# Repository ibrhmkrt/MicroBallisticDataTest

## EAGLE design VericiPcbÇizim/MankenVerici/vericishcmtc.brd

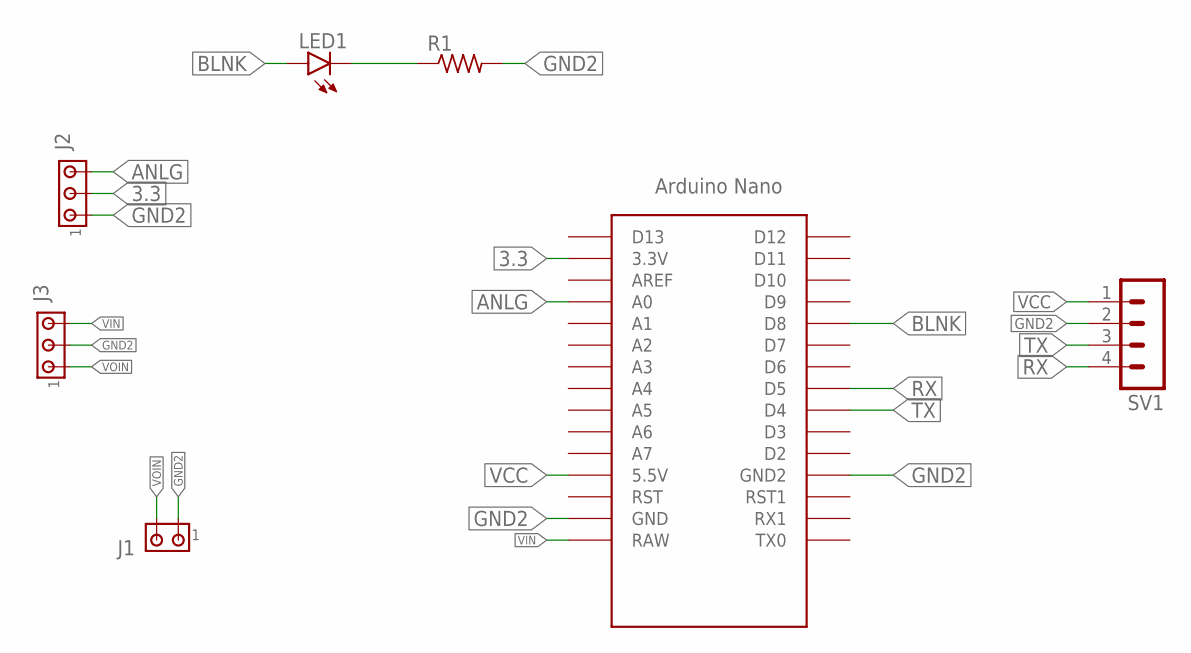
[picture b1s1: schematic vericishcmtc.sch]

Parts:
J1: MTA02-100; 10X02MTA
J2, J3: MTA03-100; 10X03MTA
LED1: LED5MM
R1: R-US_0204/5; 0204/5
SV1: MA04-1
U$1: NANO

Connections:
3.3: J2.2, U$1.3.3V
ANLG: J2.3, U$1.A0
BLNK: LED1.A, U$1.D8
GND2: J1.1, J2.1, J3.2, R1.2, SV1.2, U$1.GND, U$1.GND1 (GND2)
unnamed: LED1.K (C), R1.1
RX: SV1.4, U$1.D5
TX: SV1.3, U$1.D4
VCC: SV1.1, U$1.5V (5.5V)
VIN: J3.3, U$1.RAW
VOIN: J1.2, J3.1

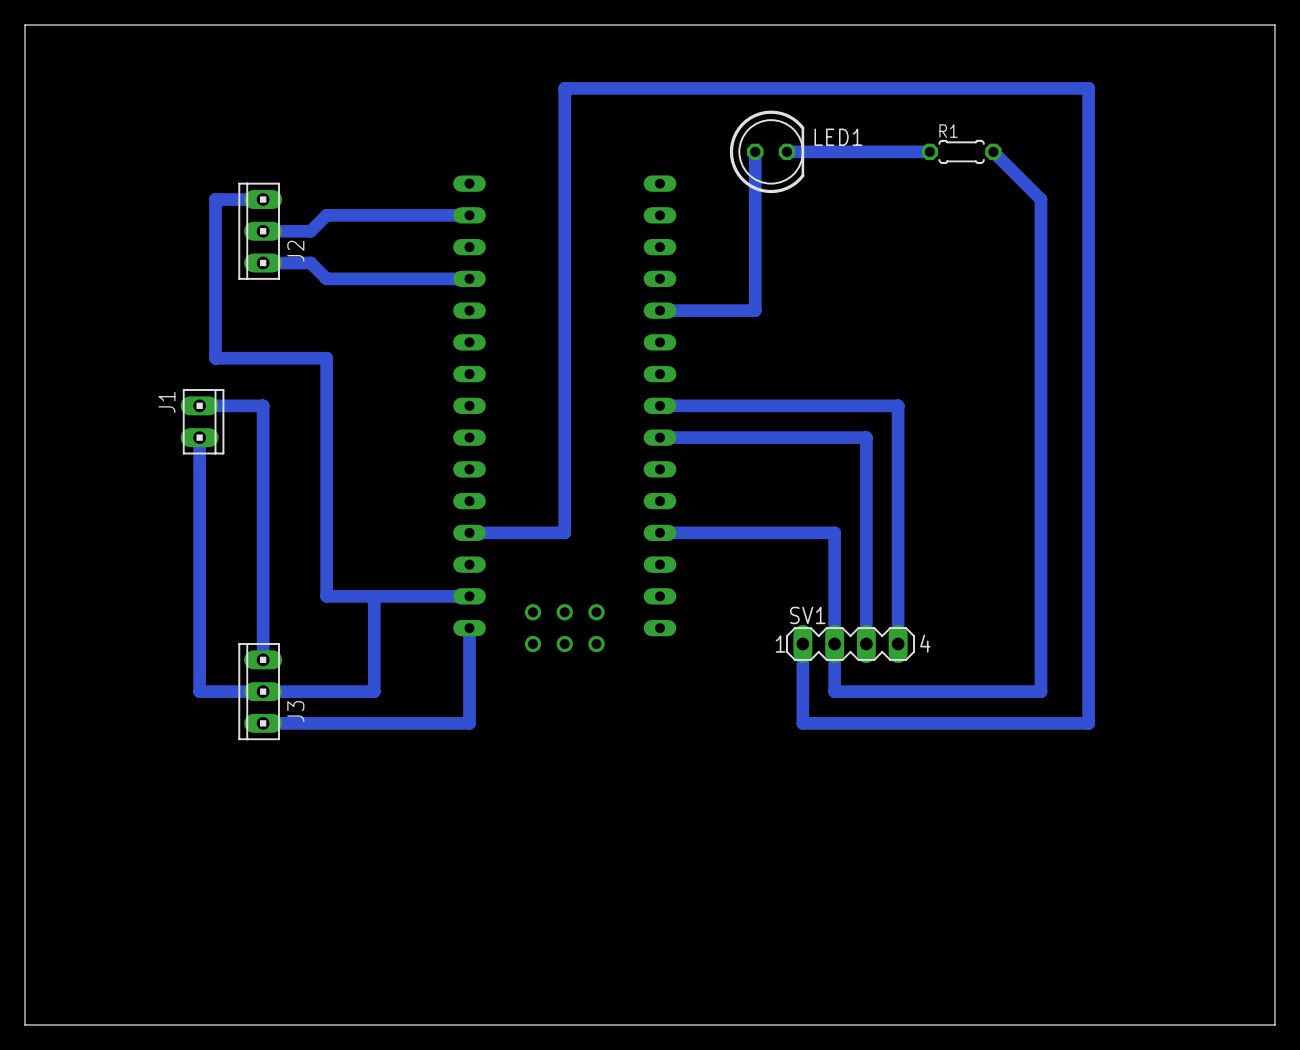
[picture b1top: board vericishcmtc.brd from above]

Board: 2 copper layers, 100.0 x 80.0 mm, 7 parts (0 on the bottom side), 10 nets.

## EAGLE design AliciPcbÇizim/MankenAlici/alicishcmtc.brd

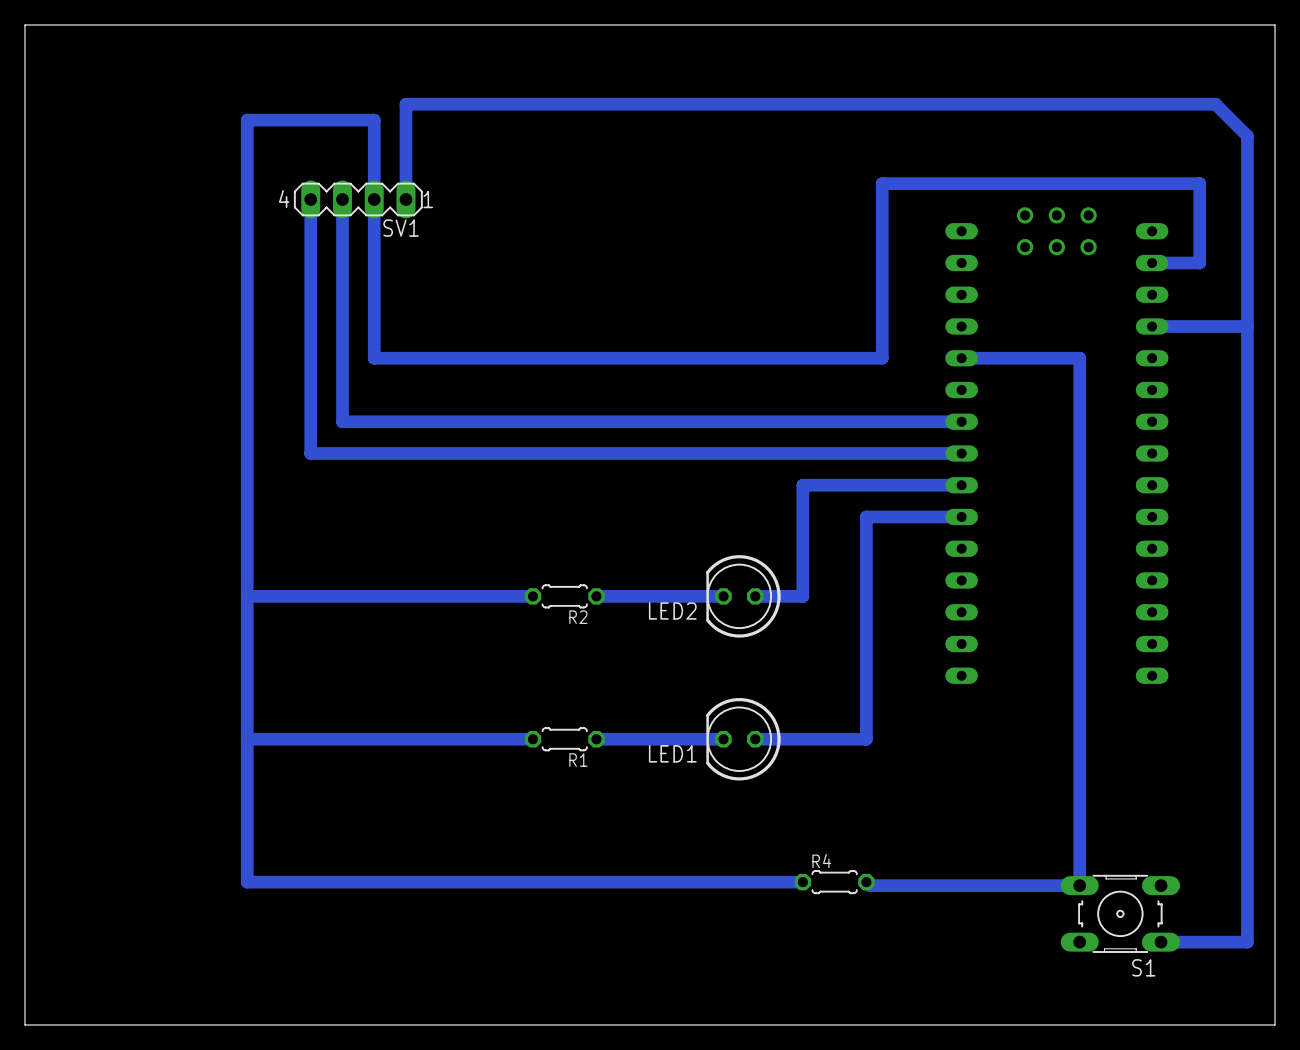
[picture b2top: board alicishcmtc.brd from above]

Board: 2 copper layers, 100.0 x 80.0 mm, 8 parts (0 on the bottom side), 9 nets.

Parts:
LED1, LED2: LED5MM
R1, R2, R4: 0204/5
S1: B3F-10XX
SV1: MA04-1
U$1: NANO

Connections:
BLNK: LED1.A, U$1.D7
GND2: R1.2, R2.2, R4.1, SV1.2, U$1.GND, U$1.GND1
unnamed: LED1.K, R1.1
unnamed: LED2.K, R2.1
RX: SV1.4, U$1.D5
SNK: LED2.A, U$1.D6
SNKBTN: R4.2, S1.4, U$1.D2
TX: SV1.3, U$1.D4
VCC: S1.1, SV1.1, U$1.5V

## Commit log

2019-10-14 Final
